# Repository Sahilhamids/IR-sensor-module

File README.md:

# PCB-Designing-Projects
Designed a two layer PCB of IR sensor module and Voltage regulator using the open source EDA KiCADsoftware.

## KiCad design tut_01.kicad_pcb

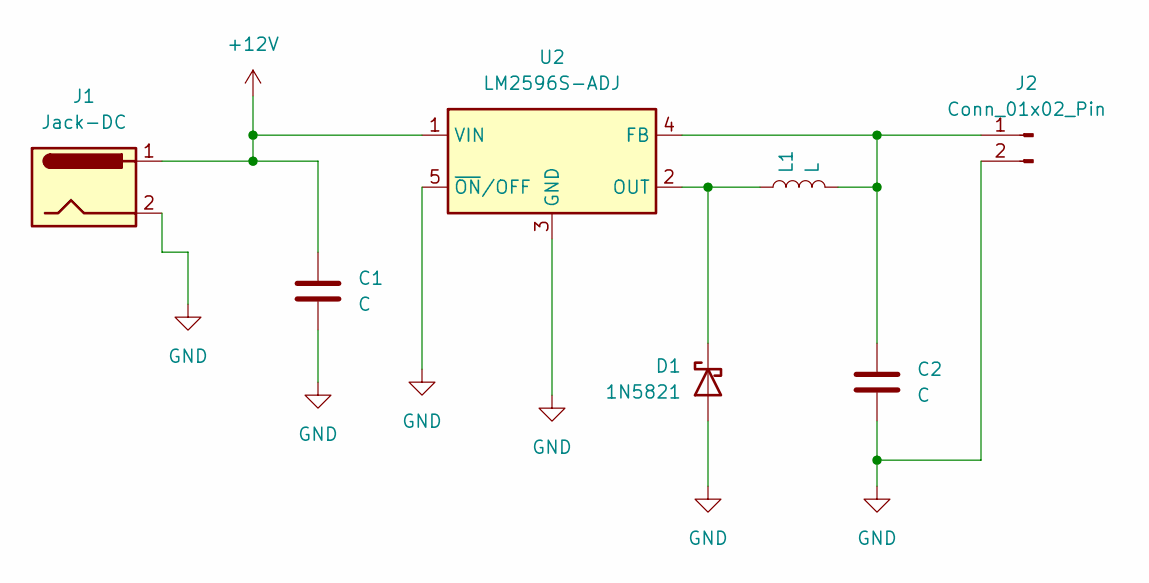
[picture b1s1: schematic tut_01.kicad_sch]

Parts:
C1, C2: C; C_0201_0603Metric_Pad0.64x0.40mm_HandSolder
D1: 1N5821; D_DO-201AD_P12.70mm_Horizontal
J1: Jack-DC; BarrelJack_SwitchcraftConxall_RAPC10U_Horizontal
J2: Conn_01x02_Pin; JWT_A3963_1x02_P3.96mm_Vertical
L1: L; L_7.3x7.3_H3.5
U2: LM2596S-ADJ; TO-263-5_TabPin3

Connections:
+12V: C1.1, J1.1, U2.1 (VIN)
GND: C1.2, C2.2, D1.2 (A), J1.2, J2.2, U2.3 (GND), U2.5 (~ON/OFF)
unnamed: D1.1 (K), L1.1, U2.2 (OUT)
unnamed: C2.1, J2.1, L1.2, U2.4 (FB)

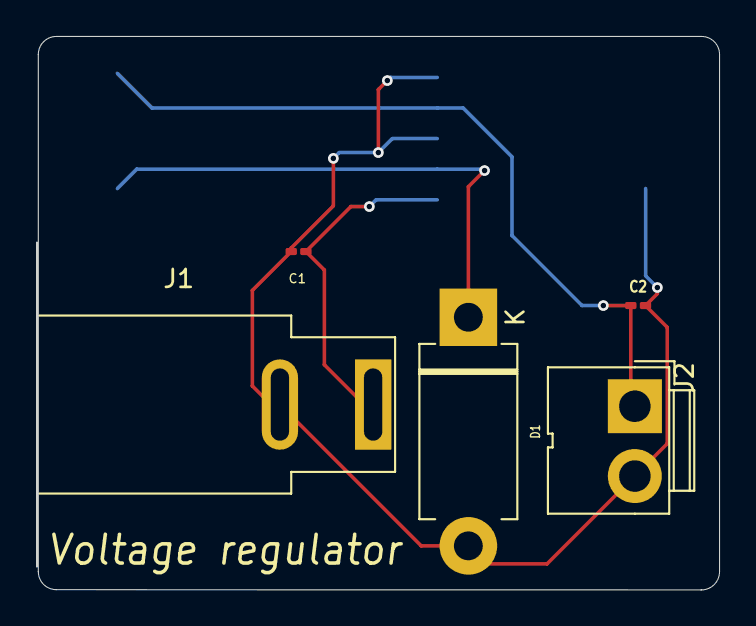
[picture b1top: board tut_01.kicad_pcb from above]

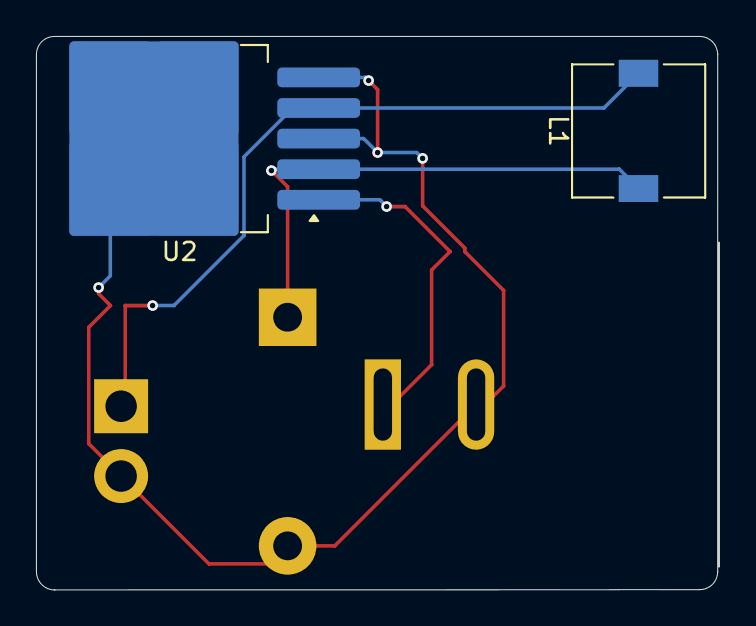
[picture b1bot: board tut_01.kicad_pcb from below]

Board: 2 copper layers, 37.9 x 30.7 mm, 7 parts (2 on the bottom side), 4 nets.

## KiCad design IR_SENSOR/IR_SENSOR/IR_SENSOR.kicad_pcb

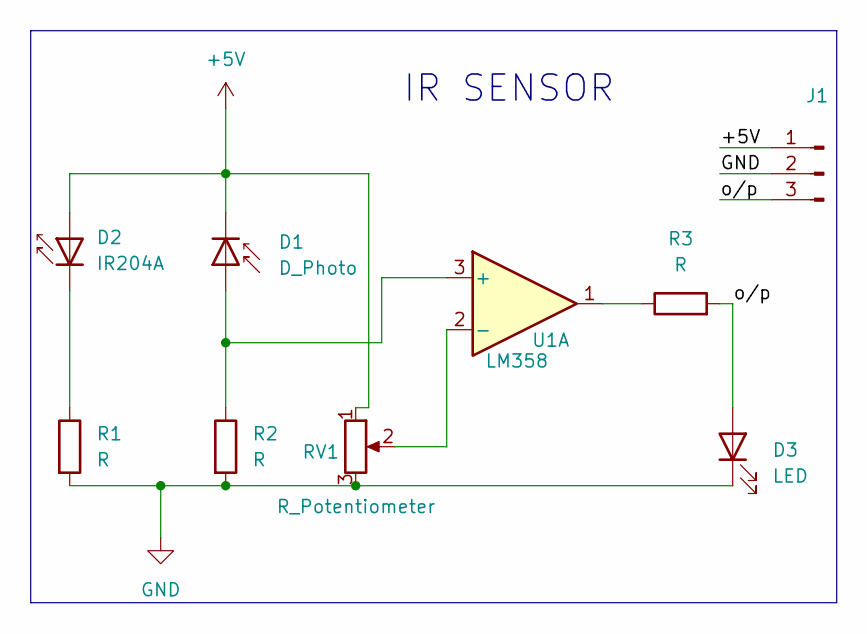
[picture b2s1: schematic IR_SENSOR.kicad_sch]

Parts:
D1: D_Photo; LED_1W_3W_R8
D2: IR204A; LED_1W_3W_R8
D3: LED; LED_1W_3W_R8
J1: Conn_01x03_Pin; PinHeader_1x03_P2.54mm_Vertical
R1: R; R_0805_2012Metric
R2, R3: R; R_0805_2012Metric_Pad1.20x1.40mm_HandSolder
RV1: R_Potentiometer; Potentiometer_ACP_CA6-VSMD_Vertical_Hole
U1: LM358; HSOP-8-1EP_3.9x4.9mm_P1.27mm_EP2.41x3.1mm_ThermalVias

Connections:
+5V: D1.1 (K), D2.2 (A), J1.1, RV1.1
/o/p: D3.2 (A), J1.3, R3.2
GND: D3.1 (K), J1.2, R1.2, R2.2, RV1.3
unnamed: D1.2 (A), R2.1, U1.3 (+)
unnamed: D2.1 (K), R1.1
unnamed: R3.1, U1.1
unnamed: RV1.2, U1.2 (-)

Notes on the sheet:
IR SENSOR

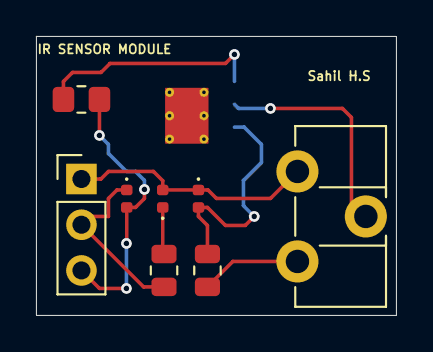
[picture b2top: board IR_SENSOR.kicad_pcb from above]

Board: 2 copper layers, 20.0 x 15.5 mm, 9 parts (1 on the bottom side), 7 nets.

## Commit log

2024-07-16 File added
2024-07-16 new file added
